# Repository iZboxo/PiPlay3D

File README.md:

# PiPlay3D
zbytek: https://github.com/Tobyy85/pi-play

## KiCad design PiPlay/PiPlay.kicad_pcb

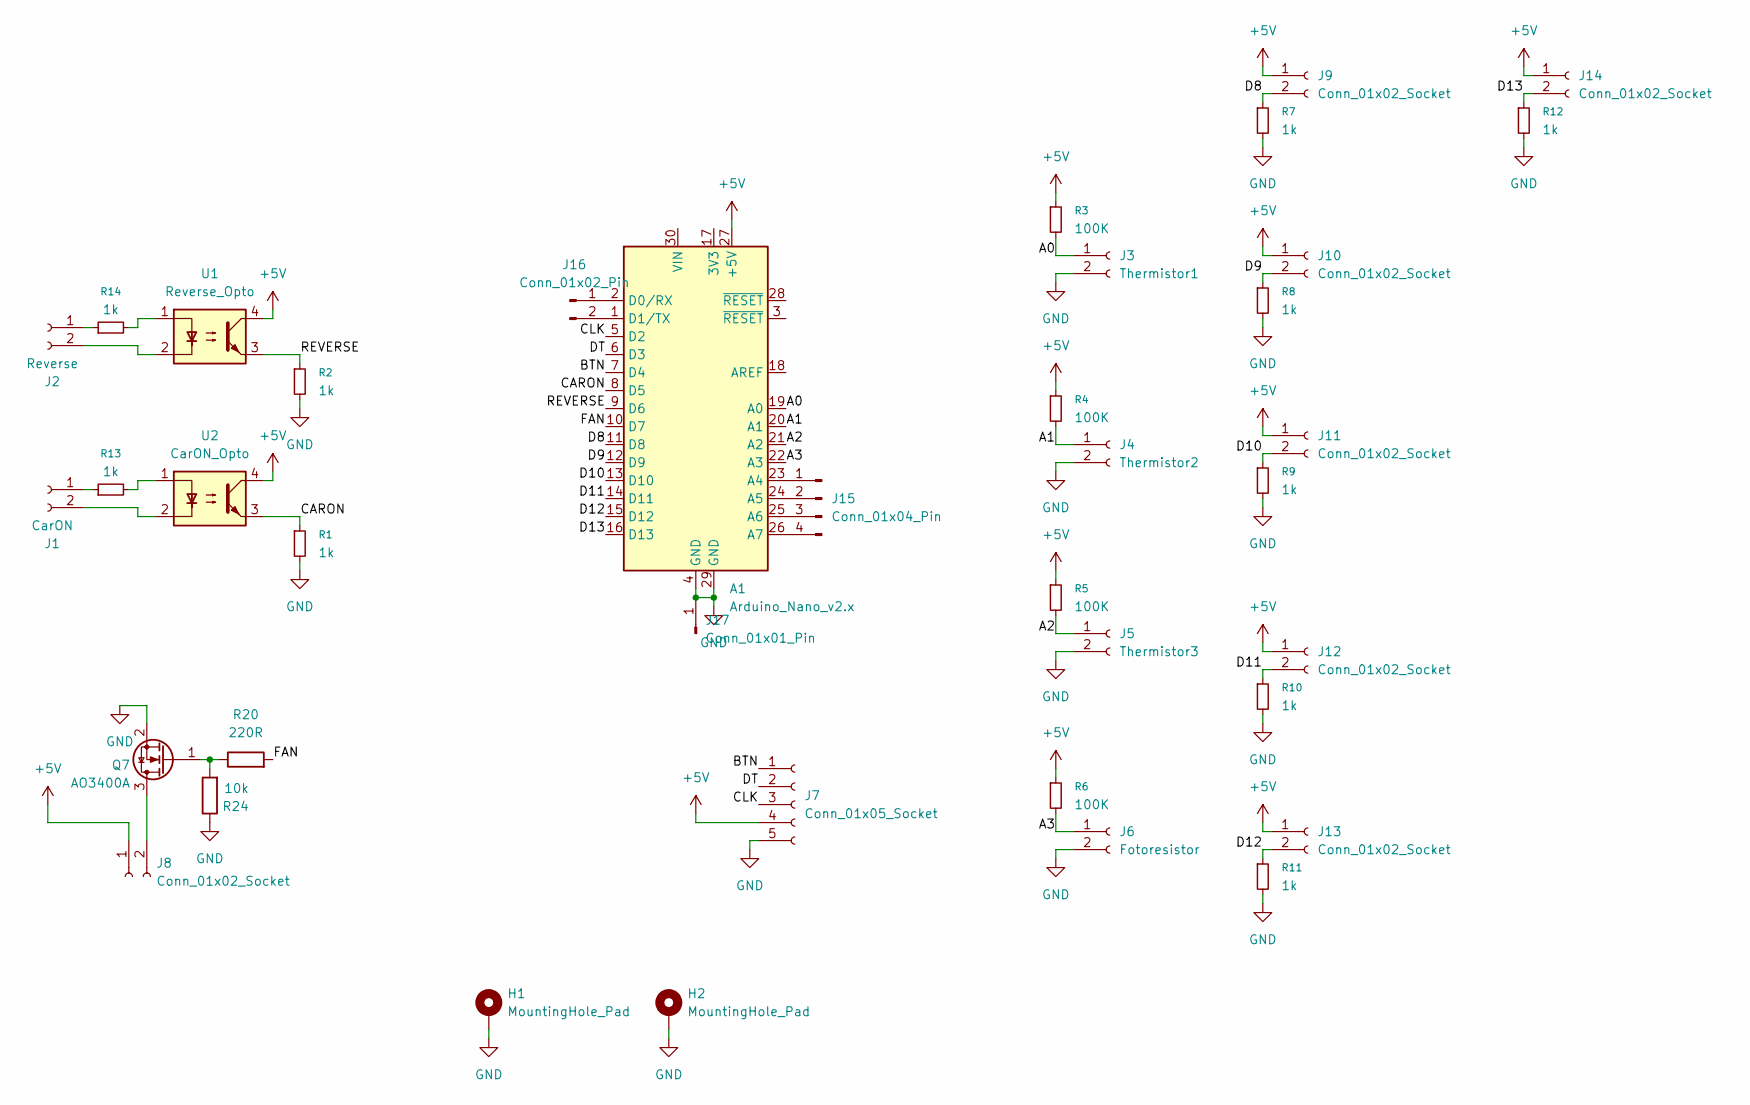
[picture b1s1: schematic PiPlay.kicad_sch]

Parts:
A1: Arduino_Nano_v2.x; Arduino_Nano
H1, H2: MountingHole_Pad; MountingHole_3.2mm_M3_Pad_Via
J1: CarON; JST_XH_B2B-XH-A_1x02_P2.50mm_Vertical
J2: Reverse; JST_XH_B2B-XH-A_1x02_P2.50mm_Vertical
J3: Thermistor1; JST_XH_B2B-XH-A_1x02_P2.50mm_Vertical
J4: Thermistor2; JST_XH_B2B-XH-A_1x02_P2.50mm_Vertical
J5: Thermistor3; JST_XH_B2B-XH-A_1x02_P2.50mm_Vertical
J6: Fotoresistor; JST_XH_B2B-XH-A_1x02_P2.50mm_Vertical
J7: Conn_01x05_Socket; JST_XH_B5B-XH-A_1x05_P2.50mm_Vertical
J8, J9, J10, J11, J12, J13, J14: Conn_01x02_Socket; JST_XH_B2B-XH-A_1x02_P2.50mm_Vertical
J15: Conn_01x04_Pin; PinHeader_1x04_P2.54mm_Vertical
J16: Conn_01x02_Pin; PinHeader_1x02_P2.54mm_Vertical
J17: Conn_01x01_Pin; PinHeader_1x01_P2.54mm_Vertical
Q7: AO3400A; SOT-23
R1, R2, R7, R8, R9, R10, R11, R12, R13, R14: 1k; R_0603_1608Metric_Pad0.98x0.95mm_HandSolder
R3, R4, R5, R6: 100K; R_0603_1608Metric_Pad0.98x0.95mm_HandSolder
R20: 220R; R_0805_2012Metric_Pad1.20x1.40mm_HandSolder
R24: 10k; R_0805_2012Metric_Pad1.20x1.40mm_HandSolder
U1: Reverse_Opto; DIP-4_W7.62mm_LongPads
U2: CarON_Opto; DIP-4_W7.62mm_LongPads

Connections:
+5V: A1.27 (+5V), J7.4, J8.1, J9.1, J10.1, J11.1, J12.1, J13.1, J14.1, R3.1, R4.1, R5.1, R6.1, U1.4, U2.4
/A0: A1.19 (A0), J3.1, R3.2
/A1: A1.20 (A1), J4.1, R4.2
/A2: A1.21 (A2), J5.1, R5.2
/A3: A1.22 (A3), J6.1, R6.2
/BTN: A1.7 (D4), J7.1
/CARON: A1.8 (D5), R1.1, U2.3
/CLK: A1.5 (D2), J7.3
/D8: A1.11 (D8), J9.2, R7.1
/D9: A1.12 (D9), J10.2, R8.1
/D10: A1.13 (D10), J11.2, R9.1
/D11: A1.14 (D11), J12.2, R10.1
/D12: A1.15 (D12), J13.2, R11.1
/D13: A1.16 (D13), J14.2, R12.1
/DT: A1.6 (D3), J7.2
/FAN: A1.10 (D7), R20.2
/REVERSE: A1.9 (D6), R2.1, U1.3
GND: A1.4 (GND), A1.29 (GND), H1.1, H2.1, J3.2, J4.2, J5.2, J6.2, J7.5, J17.1, Q7.2 (S), R1.2, R2.2, R7.2, R8.2, R9.2, R10.2, R11.2, R12.2, R24.1
unnamed: A1.23 (A4), J15.1
unnamed: A1.24 (A5), J15.2
unnamed: A1.25 (A6), J15.3
unnamed: A1.26 (A7), J15.4
unnamed: A1.2 (D0/RX), J16.1
unnamed: A1.1 (D1/TX), J16.2
unnamed: J1.1, R13.1
unnamed: J1.2, U2.2
unnamed: J2.1, R14.1
unnamed: J2.2, U1.2
unnamed: J8.2, Q7.3 (D)
unnamed: Q7.1 (G), R20.1, R24.2
unnamed: R13.2, U2.1
unnamed: R14.2, U1.1

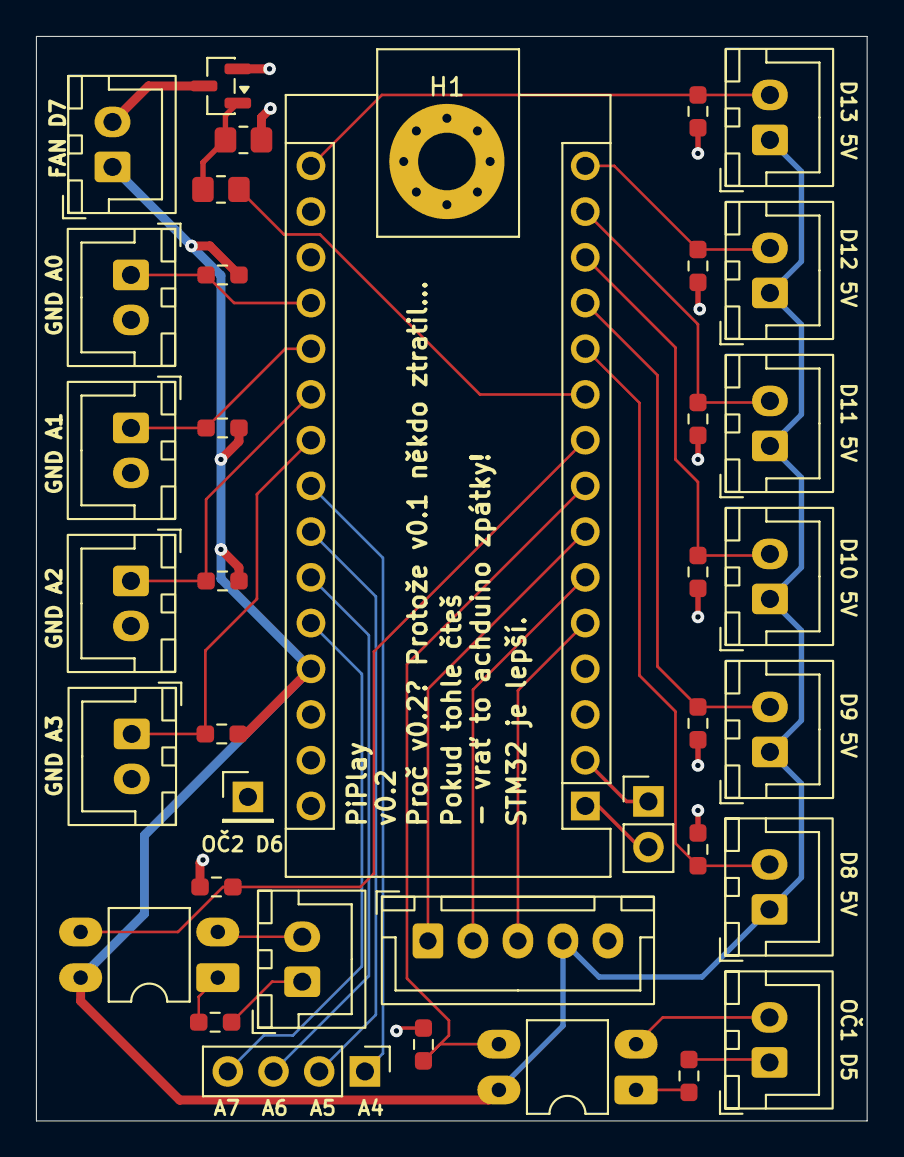
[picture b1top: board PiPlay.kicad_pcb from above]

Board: 2 copper layers, 46.2 x 60.2 mm, 38 parts (0 on the bottom side), 32 nets.

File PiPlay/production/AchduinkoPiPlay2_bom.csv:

Designator,Footprint,Quantity,Value,LCSC Part #
A1,Arduino_Nano,1,Arduino_Nano_v2.x,
J1,JST_XH_B2B-XH-A_1x02_P2.50mm_Vertical,1,CarON,
"J10, J11, J12, J13, J14, J8, J9",JST_XH_B2B-XH-A_1x02_P2.50mm_Vertical,7,Conn_01x02_Socket,
J15,PinHeader_1x04_P2.54mm_Vertical,1,Conn_01x04_Pin,
J16,PinHeader_1x02_P2.54mm_Vertical,1,Conn_01x02_Pin,
J17,PinHeader_1x01_P2.54mm_Vertical,1,Conn_01x01_Pin,
J2,JST_XH_B2B-XH-A_1x02_P2.50mm_Vertical,1,Reverse,
J3,JST_XH_B2B-XH-A_1x02_P2.50mm_Vertical,1,Thermistor1,
J4,JST_XH_B2B-XH-A_1x02_P2.50mm_Vertical,1,Thermistor2,
J5,JST_XH_B2B-XH-A_1x02_P2.50mm_Vertical,1,Thermistor3,
J6,JST_XH_B2B-XH-A_1x02_P2.50mm_Vertical,1,Fotoresistor,
J7,JST_XH_B5B-XH-A_1x05_P2.50mm_Vertical,1,Conn_01x05_Socket,
Q7,SOT-23,1,AO3400A,
"R1, R10, R11, R12, R13, R14, R2, R7, R8, R9",0603,10,1k,
R20,0805,1,220R,
R24,0805,1,10k,
"R3, R4, R5, R6",0603,4,100K,
U1,DIP-4_W7.62mm_LongPads,1,Reverse_Opto,
U2,DIP-4_W7.62mm_LongPads,1,CarON_Opto,

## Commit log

2026-04-29 Add project link to README.md
